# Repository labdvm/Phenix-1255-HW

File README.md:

<p align="center">
  <picture>
    <source media="(prefers-color-scheme: dark)" srcset="documentation/images/phenix-1255_logo_white.png">
    
  </picture>
</p>

<p align="center">
  <b>"Pi-less" SX1255 RF shield for the NXP FRDM-MCXN947</b><br>
  KiCad hardware design · separate RX/TX paths · 38.4 MHz TCXO · HS USB or Ethernet via the FRDM board
</p>

<p align="center">

</p>

<p align="center">
  <a href="#overview">Overview</a> ·
  <a href="#board-variants">Board variants</a> ·
  <a href="#features">Features</a> ·
  <a href="#preview">Preview</a> ·
  <a href="#documentation">Documentation</a> ·
  <a href="#repository-contents">Repository contents</a> ·
  <a href="#getting-started">Getting started</a> ·
  <a href="#license">License</a>
</p>

## Overview

Phenix-1255 is a shield board that pairs the popular **Semtech SX1255** RF transceiver with the
**NXP FRDM-MCXN947** development board — no Raspberry Pi required. The MCX N947 handles the
I/Q sample stream and talks to the host PC over **High-Speed USB** or **Ethernet**.

The project idea comes from **[DM5LF](https://github.com/w4tchd0g)**, who also writes the software. The hardware was designed by **[Z32IT](https://github.com/labdvm)**.

| | |
|---|---|
| 🧠 **Controller** | NXP FRDM-MCXN947 (plugs directly onto the shield headers) |
| 📡 **RF transceiver** | Semtech SX1255 (I/Q, 400–510 MHz) |
| ⏱️ **Reference clock** | 38.4 MHz TCXO, 0.5–1 ppm |
| 🔌 **Host link** | High-Speed USB 2.0 or Ethernet of the FRDM-MCXN947 |
| ⚡ **Power** | 5 V from the FRDM-MCXN947 (USB-C); PoE operation possible with a 48 V → 5 V USB-C PoE splitter |
| 📐 **PCB** | 118 × 55 mm, 2 layers, 1.2 mm thickness |

## Board variants

The repository contains two variants of revision V2. Both share the same board outline, headers,
power supply, user interface and RX path.

| Variant | Folder | Difference |
|---|---|---|
| **V2** | [`FRDM-SX1255/`](FRDM-SX1255) | SX1255 TX output → low-pass filter → U.FL |
| **V2 Plus** | [`FRDM-SX1255+/`](FRDM-SX1255+) | Additional **TX driver amplifier** (Qorvo TQP3M9036, U2) between the SX1255 and the low-pass filter, with a resistive π-attenuator (R10–R12) at its input. The amplifier runs from 5 V and is switched together with the PA via `~PA_EN`. |

## Features

- **Separate RX and TX paths** with U.FL connectors (*TX* JJ1, *RX* JJ2)
  - RX: SAW band-pass filter (Tai-Saw TA0655A, 430 MHz centre frequency, 2 MHz bandwidth) → LC matching → `RFI`
  - TX: `RFO_P` → low-pass filter (Mini-Circuits LFCN-490+) → U.FL; V2 Plus adds the TQP3M9036 driver amplifier
- **Switchable PA supply** – P-MOSFET (DMP1045U) controlled by `~PA_EN`
- **Power supply** – resettable 500 mA fuse, TVS diode array (SP0502BAHT), ferrite bead and 3.3 V LDO (MCP1703)
- **User interface**
  - Three push buttons: *Left*, *OK*, *Right*
  - Socket for an I²C OLED display
  - Status LEDs: *PWR*, *Good*, *Info*, *Err*

## Preview

### V2

| Top | Bottom |
|:---:|:---:|
|  |  |

### V2 Plus

| Top | Bottom |
|:---:|:---:|
|  |  |

The images are rendered from the `.kicad_pcb` files with the KiCad 3D renderer and show the fully
assembled board with a 0.96″ OLED module plugged into its socket (J7), including the parts that are
marked *do not populate* in the layout (FRDM headers, OLED socket and, on V2 Plus, the SAW filter).
After changing the layout, run [`./scripts/render.sh`](scripts/render.sh) to update the images.

### 3D models

Every part on the board has a 3D model, so the board can be checked mechanically (e.g. for an
enclosure) and exported as STEP from KiCad. Most models come from the KiCad standard library
(`${KICAD10_3DMODEL_DIR}`); parts without a matching library model use these substitutes:

| Part | Footprint | 3D model | Source |
|---|---|---|---|
| FRDM headers J1, J2, J3, J4, J9, J12 | Samtec SSQ (FRDM template) | `PinHeader_2xNN_P2.54mm_Vertical` | KiCad library, mounted below the board |
| U.FL connectors JJ1 *TX* / JJ2 *RX* | `U.FL_Molex_MCRF_73412-0110_Vertical` | `U.FL_Hirose_U.FL-R-SMT-1_Vertical`, rotated 90° | KiCad library (no model for the Molex footprint) |
| Push buttons SW1–SW3 | `PTS647SK38SMTR2LFS` | `SW_SPST_PTS647Sx70` (stand-in for the E-Switch TL3305 in the BOM) | KiCad library |
| SAW filter X1 (TA0655A) | `Filter_SAW-6_3.8x3.8mm` | [`3dmodels/TA0655A.stp`](FRDM-SX1255/3dmodels/TA0655A.stp) | Project file |
| TX amplifier U2 (V2 Plus) | `SON50P200X200X95-9N` | `VDFN-8-1EP_2x2mm_P0.5mm_EP0.9x1.7mm` | KiCad library |
| OLED display (plugged into J7) | `PinSocket_1x04_P2.54mm_Vertical` | [`3dmodels/OLED_0.96in_128x64_I2C.stp`](FRDM-SX1255/3dmodels/OLED_0.96in_128x64_I2C.stp) – 0.96″ 128×64 SSD1306 I²C module, as a second model on the socket | Project file |

Mounting holes need no model.

The shield is designed for the NXP FRDM-MCXN947 development board, see the
[NXP FRDM-MCXN947 product page](https://www.nxp.com/design/design-center/development-boards-and-designs/FRDM-MCXN947)
for photos, documentation and the board pinout.

## Documentation

| Document | Content |
|---|---|
| [Hardware](documentation/hardware.md) | Block overview, header pin assignment, PA supply, power supply, V2 Plus amplifier, changes in the current layout |
| [Manufacturing and assembly](documentation/manufacturing.md) | PCB specification, production files, assembly notes, first power-up |

## Host PC requirements

| Component | Minimum |
|---|---|
| Interface | USB 2.0 (High-Speed) or Ethernet |
| CPU | Intel or AMD, 4 cores |
| RAM | 4 GB DDR3 |
| Storage | SSD |
| OS | Xubuntu x64 |

## Repository contents

Each board variant is a self-contained KiCad project in its own folder:

```
Phenix-1255-HW/
├── FRDM-SX1255/                      # V2
│   ├── FRDM-SX1255-V2.kicad_pro      # KiCad project – open this one
│   ├── FRDM-SX1255-V2.kicad_sch      # schematic
│   ├── FRDM-SX1255-V2.kicad_pcb      # PCB layout
│   ├── FRDM-SX1255-V2.pdf            # schematic as PDF
│   ├── FRDM-SX1255-V2.png / _b.png   # 2D board views (KiCad export)
│   ├── 3dmodels/                     # project-specific 3D models
│   └── Gerber and BOM/               # manufacturing data
│       ├── …_gerber.zip              # Gerber and drill files for PCB fabrication
│       ├── …_bom.csv                 # bill of materials (incl. DigiKey part numbers)
│       ├── …_positions.csv           # pick-and-place positions for assembly
│       └── …_netlist.ipc             # IPC-D-356 netlist for electrical testing
├── FRDM-SX1255+/                     # V2 Plus – same structure, files named "FRDM-SX1255+ V2.*"
├── documentation/                    # hardware and manufacturing documentation, images
└── scripts/render.sh                 # renders the PCB images (needs kicad-cli)
```

| Quick links | V2 | V2 Plus |
|---|---|---|
| Schematic (PDF) | [`FRDM-SX1255-V2.pdf`](FRDM-SX1255/FRDM-SX1255-V2.pdf) | [`FRDM-SX1255+ V2.pdf`](FRDM-SX1255+/FRDM-SX1255+%20V2.pdf) |
| Gerber | [`…_gerber.zip`](FRDM-SX1255/Gerber%20and%20BOM/FRDM-SX1255-V2.kicad_pcb_gerber.zip) | [`…_gerber.zip`](FRDM-SX1255+/Gerber%20and%20BOM/FRDM-SX1255+%20V2.kicad_pcb_gerber.zip) |
| BOM | [`…_bom.csv`](FRDM-SX1255/Gerber%20and%20BOM/FRDM-SX1255-V2.kicad_pcb_bom.csv) | [`…_bom.csv`](FRDM-SX1255+/Gerber%20and%20BOM/FRDM-SX1255+%20V2.kicad_pcb_bom.csv) |
| Positions | [`…_positions.csv`](FRDM-SX1255/Gerber%20and%20BOM/FRDM-SX1255-V2.kicad_pcb_positions.csv) | [`…_positions.csv`](FRDM-SX1255+/Gerber%20and%20BOM/FRDM-SX1255+%20V2.kicad_pcb_positions.csv) |

## Getting started

1. **Choose a variant** – V2, or V2 Plus if you want the additional TX driver amplifier.
2. **Order the PCB** – upload the Gerber ZIP to a PCB manufacturer of your choice
   (2 layers, **1.2 mm** board thickness). For assembly, provide the BOM and position files as well.
   Details: [Manufacturing and assembly](documentation/manufacturing.md).
3. **Assemble** the shield and plug it onto the FRDM-MCXN947.
4. **Connect antennas / RF cabling** to the U.FL connectors *TX* (JJ1) and *RX* (JJ2).
5. **Install the software** from [phenix-1255-sw](https://github.com/w4tchd0g/phenix-1255-sw).

## Related projects

- 💻 **Software:** [w4tchd0g/phenix-1255-sw](https://github.com/w4tchd0g/phenix-1255-sw)

## Credits

- **Idea & software:** DM5LF – [@w4tchd0g](https://github.com/w4tchd0g)
- **Hardware design:** Z32IT – [@labdvm](https://github.com/labdvm)

## License

Copyright © Z32IT 2026.

This source describes Open Hardware and is licensed under the **CERN-OHL-P v2**.

You may redistribute and modify this source and make products using it under the terms of the
[CERN-OHL-P v2](https://ohwr.org/cern_ohl_p_v2.txt). This source is distributed **WITHOUT ANY EXPRESS
OR IMPLIED WARRANTY, INCLUDING OF MERCHANTABILITY, SATISFACTORY QUALITY AND FITNESS FOR A PARTICULAR
PURPOSE**. Please see the CERN-OHL-P v2 for applicable conditions.

Source location: <https://github.com/labdvm/Phenix-1255-HW>

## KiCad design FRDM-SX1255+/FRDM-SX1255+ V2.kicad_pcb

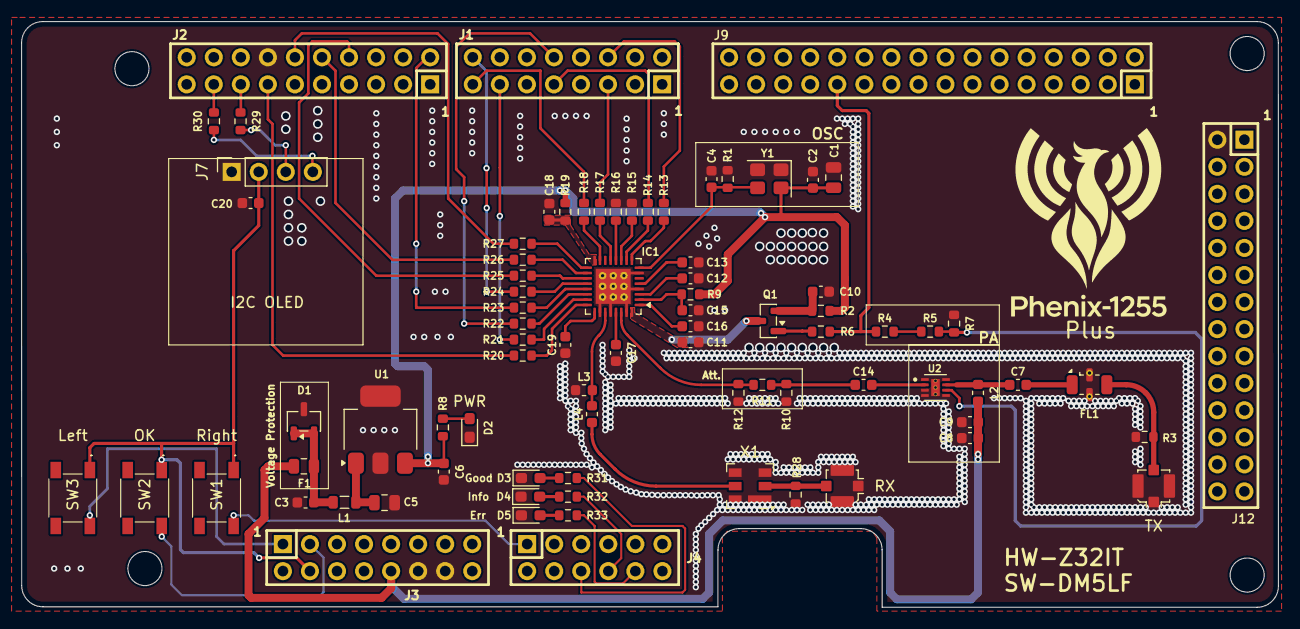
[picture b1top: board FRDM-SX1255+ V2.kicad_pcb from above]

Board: 2 copper layers, 118.0 x 55.0 mm, 86 parts (0 on the bottom side), 66 nets.

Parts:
C1, C5: 22u; C_0805_2012Metric
C2, C11, C12, C13, C19, C20: 100n; C_0603_1608Metric
C3, C6, C8, C10, C15, C18: 1u; C_0603_1608Metric
C4: 10p; C_0603_1608Metric
C7, C9, C14, C17: 100p; C_0603_1608Metric
C16: 10n; C_0603_1608Metric
D1: SP0502BAHT; SOT-23-3
D2: PWR; LED_0603_1608Metric_Pad1.05x0.95mm_HandSolder
D3: Good; LED_0603_1608Metric_Pad1.05x0.95mm_HandSolder
D4: Info; LED_0603_1608Metric_Pad1.05x0.95mm_HandSolder
D5: Err; LED_0603_1608Metric_Pad1.05x0.95mm_HandSolder
F1: 500mA; Fuse_0805_2012Metric
FL1: LFCN-490; Filter_Mini-Circuits_FV1206
H1, H2, H3, H4: Mechanical_MountingHole; MOUNTINGHOLE_3.2MM_M3
IC1: SX1255; QFN-32-1EP_5x5mm_P0.5mm_EP3.3x3.3mm_ThermalVias
J1, J3: SSQ-108-03-T-D
J2: SSQ-110-03-T-D
J4: SSQ-106-03-T-D
J7: I2C OLED; PinSocket_1x04_P2.54mm_Vertical
J9: SSQ-116-03-T-D
J12: SSQ-114-03-T-D
JJ1: TX; U.FL_Molex_MCRF_73412-0110_Vertical
JJ2: RX; U.FL_Molex_MCRF_73412-0110_Vertical
L1: 600 ohm/100MHz; L_0805_2012Metric
L2: 68nH; L_0603_1608Metric
L3: 82n; L_0603_1608Metric
L4: 39n; L_0603_1608Metric
Q1: DMP1045U; SOT-23
R1, R7: 10K; R_0603_1608Metric
R2, R4, R9, R19: 1R; R_0603_1608Metric
R3, R28: 1M; R_0603_1608Metric
R5: 33K; R_0603_1608Metric
R6, R15, R16, R17, R24, R25, R27: 330R; R_0603_1608Metric
R8: 3K3; R_0603_1608Metric
R10, R12: 150R; R_0603_1608Metric
R11: 36R; R_0603_1608Metric
R13, R14, R18, R20, R21, R22, R23, R26, R29, R30: 33R; R_0603_1608Metric
R31, R32, R33: 1K5; R_0603_1608Metric
SW1: Right; PTS647SK38SMTR2LFS
SW2: OK; PTS647SK38SMTR2LFS
SW3: Left; PTS647SK38SMTR2LFS
U1: MCP1703Ax-330xxDB; SOT-223-3_TabPin2
U2: TQP3M9036; SON50P200X200X95-9N
X1: TA0655A; Filter_SAW-6_3.8x3.8mm
Y1: 38.4MHz; Crystal_SMD_3225-4Pin_3.2x2.5mm

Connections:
+3V3: C1.2, C2.1, C6.1, R2.2, R8.2, R9.2, R19.1, U1.3 (VO), Y1.4 (VDD)
+5V0: C8.2, C9.1, F1.1, J3.10, L2.1
/+3.3V: C20.2, J3.4, J7.2, SW1.1, SW2.1, SW3.1
/BTN_LEFT: J3.1, SW3.2
/BTN_OK: J3.3, SW2.2
/BTN_RIGHT: J4.1, SW1.2
/CK_OUT: J1.9, R14.1
/DIO0: J2.2, R23.1
/DIO1: J1.10, R22.1
/DIO2: J1.13, R21.1
/DIO3: J2.13, R20.1
/I_IN: J1.5, R17.1
/I_OUT: J1.15, R18.1
/MISO: J2.10, R26.1
/MOSI: J2.8, R25.1
/NSS: J1.16, R24.1
/RF-out: C7.1, L2.2, U2.7
/RST: J1.6, R13.1
/SCK: J2.12, R27.1
/SCL_oled: J2.15, R29.2
/SDA_oled: J2.17, R30.2
/SX_CK_IN: IC1.11 (CK_IN), R15.2
/SX_CK_OUT: IC1.10 (CK_OUT), R14.2
/SX_DIO0: IC1.21 (DIO0), R23.2
/SX_DIO1: IC1.22 (DIO1), R22.2
/SX_DIO2: IC1.23 (DIO2), R21.2
/SX_DIO3: IC1.24 (DIO3), R20.2
/SX_I_IN: IC1.13 (I_IN), R17.2
/SX_I_OUT: IC1.15 (I_OUT), R18.2
/SX_MISO: IC1.18 (MISO), R26.2
/SX_MOSI: IC1.19 (MOSI), R25.2
/SX_NSS: IC1.20 (NSS), R24.2
/SX_Q_IN: IC1.12 (Q_IN), R16.2
/SX_RESET: IC1.9 (RESET), R13.2
/SX_RFI: IC1.27 (RFI), L3.2, L4.2
/SX_RFO_N: C17.2, IC1.29 (RFO_N)
/SX_RFO_P: IC1.30 (RFO_P), R11.1, R12.1
/SX_SCK: IC1.17 (SCK), R27.2
/SX_VBAT2: C18.1, IC1.16 (VBAT2), R19.2
/SX_VBAT3: C11.1, IC1.32 (VBAT3), Q1.3 (D)
/SX_VBATI: C15.1, IC1.2 (VBATI), R9.1
/SX_VR_ANA2: C19.2, IC1.25 (VR_ANA2)
/SX_VR_ANAI: C12.2, IC1.3 (VR_ANAI)
/SX_VR_DIG: C13.2, IC1.5 (VR_DIG)
/SX_VR_PA: C16.2, IC1.1 (VR_PA)
/TCXO: C4.1, IC1.8 (XTB), R1.1, Y1.3 (OUT)
/~PA_EN: J9.23 (Pin_23_23), R4.2, R6.1
GND: C1.1, C2.2, C3.2, C4.2, C5.2, C6.2, C8.1, C9.2, C10.2, C11.2, C12.1, C13.1, C15.2, C16.1, C17.1, C18.2, C19.1, C20.1, D1.3 (A), D2.1 (K), D3.1 (K), D4.1 (K), D5.1 (K), FL1.2 (GND), FL1.4 (GND), IC1.4 (GND_1), IC1.7 (GND_2), IC1.26 (GND_3), IC1.28 (GND_4), IC1.31 (GND_5), IC1.33 (GND_6), J2.14, J3.12, J3.14, J7.1, J12.2, JJ1.2 (Ext), JJ2.2 (Ext), L3.1, R1.2, R3.1, R7.1, R10.2, R12.2, R15.1, R16.1, R28.1, U1.2 (GND), U2.1, U2.3, U2.4, U2.5, U2.8, U2.9, U2.V1, U2.V2, U2.V3, X1.1 (GND), X1.3 (GND), X1.4 (GND), X1.6 (GND), Y1.1 (Tri-State), Y1.2 (GND)
unnamed: C3.1, D1.1 (K), D1.2 (K), F1.2, L1.1
unnamed: C14.1, R10.1, R11.2
unnamed: C14.2, U2.2
unnamed: D2.2 (A), R8.1
unnamed: D3.2 (A), R31.2
unnamed: D4.2 (A), R32.2
unnamed: D5.2 (A), R33.2
unnamed: C7.2, FL1.1 (IN)
unnamed: FL1.3 (OUT), JJ1.1 (In), R3.2
unnamed: J7.3, R29.1
unnamed: J7.4, R30.1
unnamed: JJ2.1 (In), R28.2, X1.2 (IN)
unnamed: Q1.1 (G), R6.2
unnamed: C10.1, Q1.2 (S), R2.1
unnamed: R4.1, R5.2
unnamed: R5.1, R7.2, U2.6
unnamed: C5.1, L1.2, U1.1 (VI)
unnamed: L4.1, X1.5 (OUT)

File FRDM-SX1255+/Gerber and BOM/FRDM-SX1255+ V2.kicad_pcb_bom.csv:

Designator,Quantity,Value,Footprint,Package,MPN,DNP,Mount_Type,KiLib_Generator,Manufacturer,Manufacturer Product Number,Description,DigiKey Part Number,Sim.Pin,TCXO-Footprints
"C1, C5",2,22u,C_0805_2012Metric,,1276-6526-1-ND,,smt,SMD_2terminal_chip_molded,Samsung Electro-Mechanics,CL21A226KOQNNNE,,,,
"C10, C15, C18, C3, C6, C8",6,1u,C_0603_1608Metric,,311-3484-1-ND,,smt,SMD_2terminal_chip_molded,YAGEO,CC0603JRX7R6BB105,,,,
"C11, C12, C13, C19, C2, C20",6,100n,C_0603_1608Metric,,720-1688-1-ND,,smt,SMD_2terminal_chip_molded,Vishay Vitramon,VJ0603Y104JXQPW1BC,,,,
"C14, C17, C7, C9",4,100p,C_0603_1608Metric,,399-15348-1-ND,,smt,SMD_2terminal_chip_molded,KEMET,C0603C101J8GACTU,,,,
C16,1,10n,C_0603_1608Metric,,399-C0603C103K8RACTUCT-ND,,smt,SMD_2terminal_chip_molded,KEMET,C0603C103K8RACTU,,,,
C4,1,10p,C_0603_1608Metric,,399-14932-1-ND,,smt,SMD_2terminal_chip_molded,KEMET,C0603C100J8GACTU,,,,
D1,1,SP0502BAHT,SOT-23-3,,,,smt,package/gullwing,Littelfuse Inc.,SP0502BAHTG,"TVS Diode Array, 5.5V Standoff, 2 Channels, SOT-23 package",F2714CT-ND,,
D2,1,PWR,LED_0603_1608Metric_Pad1.05x0.95mm_HandSolder,,160-LTST-T180UWETCT-ND,,smt,SMD_2terminal_chip_molded,Lite-On Inc.,LTST-T180UWET,"Light emitting diode, small symbol",,1=K 2=A,
D3,1,Good,LED_0603_1608Metric_Pad1.05x0.95mm_HandSolder,,754-APT1608SGD3CT-ND,,smt,SMD_2terminal_chip_molded,Kingbright,APT1608SGD3,"Light emitting diode, small symbol",,1=K 2=A,
D4,1,Info,LED_0603_1608Metric_Pad1.05x0.95mm_HandSolder,,160-1437-1-ND,,smt,SMD_2terminal_chip_molded,Lite-On Inc.,LTST-C190KSKT,"Light emitting diode, small symbol",,1=K 2=A,
D5,1,Err,LED_0603_1608Metric_Pad1.05x0.95mm_HandSolder,,160-1479-1-ND,,smt,SMD_2terminal_chip_molded,Lite-On Inc.,LTST-S270KRKT,"Light emitting diode, small symbol",,1=K 2=A,
F1,1,500mA,Fuse_0805_2012Metric,,,,smt,SMD_2terminal_chip_molded,Littelfuse Inc.,0805L050WR,"Resettable fuse, polymeric positive temperature coefficient, small symbol",F2772CT-ND,,
FL1,1,LFCN-490,Filter_Mini-Circuits_FV1206,,3157-LFCN-490+CT-ND,,smt,,Mini-Circuits,LFCN-490+,,,,
"H1, H2, H3, H4",4,Mechanical_MountingHole,MOUNTINGHOLE_3.2MM_M3,,,,tht,,,,,,,
IC1,1,SX1255,QFN-32-1EP_5x5mm_P0.5mm_EP3.3x3.3mm_ThermalVias,,SX1255IWLTRTCT-ND,,smt,package/no_lead,Semtech Corporation,SX1255IWLTRT,,,,
J9,1,~,SSQ-116-03-T-D,,,,tht,,,,"Generic connector, double row, 02x16, odd/even pin numbering scheme (row 1 odd numbers, row 2 even numbers), script generated (kicad-library-utils/schlib/autogen/connector/)",,,
JJ1,1,TX,U.FL_Molex_MCRF_73412-0110_Vertical,,343-CONMHF1-SMD-G-TCT-ND,,smt,,TE Connectivity Linx,CONMHF1-SMD-G-T,,,,
JJ2,1,RX,U.FL_Molex_MCRF_73412-0110_Vertical,,343-CONMHF1-SMD-G-TCT-ND,,smt,,TE Connectivity Linx,CONMHF1-SMD-G-T,,,,
L1,1,600 ohm/100MHz,L_0805_2012Metric,,490-1046-1-ND,,smt,SMD_2terminal_chip_molded,Murata Electronics,BLM21BD601SN1D,FERRITE BEAD 600 OHM 0805 1LN,,,
L2,1,68nH,L_0603_1608Metric,,490-1178-1-ND,,smt,SMD_2terminal_chip_molded,Murata Electronics,LQW18AN68NJ00D,,,,
L3,1,82n,L_0603_1608Metric,,490-LQW18AS82NG00DCT-ND,,smt,SMD_2terminal_chip_molded,Murata Electronics,LQW18AS82NG00D,,,,
L4,1,39n,L_0603_1608Metric,,490-LQW18AS39NG00DCT-ND,,smt,SMD_2terminal_chip_molded,Murata Electronics,LQW18AS39NG00D,,,,
Q1,1,DMP1045U,SOT-23,,BSS84-TPMSCT-ND,,smt,package/gullwing,Diodes Incorporated,DMP1045UQ-7,P-Channel 12 V 2.6A (Ta) 530mW,31-DMP1045UQ-7CT-ND,,
"R1, R7",2,10K,R_0603_1608Metric,,541-10.0KHCT-ND,,smt,SMD_2terminal_chip_molded,Vishay Dale,CRCW060310K0FKEA,,,,
"R10, R12",2,150R,R_0603_1608Metric,,YAG1533CT-ND,,smt,SMD_2terminal_chip_molded,YAGEO,RT0603BRD07150RL,,,,
R11,1,36R,R_0603_1608Metric,,13-RT0603BRC0736RLCT-ND,,smt,SMD_2terminal_chip_molded,YAGEO,RT0603BRC0736RL,,,,
"R13, R14, R18, R20, R21, R22, R23, R26, R29, R30",10,33R,R_0603_1608Metric,,541-33.0HCT-ND,,smt,SMD_2terminal_chip_molded,Vishay Dale,CRCW060333R0FKEA,,,,
"R15, R16, R17, R24, R25, R27, R6",7,330R,R_0603_1608Metric,,541-330HCT-ND,,smt,SMD_2terminal_chip_molded,Vishay Dale,CRCW0603330RFKEA,,,,
"R19, R2, R9",3,1R,R_0603_1608Metric,,P17371CT-ND,,smt,SMD_2terminal_chip_molded,Panasonic Industry,ERJ-3BQF1R0V,,,,
"R28, R3",2,1M,R_0603_1608Metric,,541-1.00MHCT-ND,,smt,SMD_2terminal_chip_molded,Vishay Dale,CRCW06031M00FKEA,,,,
"R31, R32, R33",3,1K5,R_0603_1608Metric,,541-1.5KGCT-ND,,smt,SMD_2terminal_chip_molded,Vishay Dale,CRCW06031K50JNEA,,,,
R4,1,1R,R_0603_1608Metric,,541-1.00HHCT-ND,,smt,SMD_2terminal_chip_molded,Vishay Dale,CRCW06031R00FKEA,,,,
R5,1,33K,R_0603_1608Metric,,541-33.0KHCT-ND,,smt,SMD_2terminal_chip_molded,Vishay Dale,CRCW060333K0FKEA,,,,
R8,1,3K3,R_0603_1608Metric,,541-3.30KHCT-ND,,smt,SMD_2terminal_chip_molded,Vishay Dale,CRCW06033K30FKEA,,,,
SW1,1,Right,PTS647SK38SMTR2LFS,,,,smt,,E-Switch,TL3305CF260QG,"Push button switch, generic, two pins",EG5355CT-ND,,
SW2,1,OK,PTS647SK38SMTR2LFS,,,,smt,,E-Switch,TL3305CF260QG,"Push button switch, generic, two pins",EG5355CT-ND,,
SW3,1,Left,PTS647SK38SMTR2LFS,,,,smt,,E-Switch,TL3305CF260QG,"Push button switch, generic, two pins",EG5355CT-ND,,
U1,1,MCP1703Ax-330xxDB,SOT-223-3_TabPin2,,MCP1703T-3302E/DBCT-ND,,smt,,Microchip Technology,MCP1703T-3302E/DB,,,,
U2,1,TQP3M9036,SON50P200X200X95-9N,,2312-TQP3M9036CT-ND,,smt,,Qorvo,TQP3M9036,,,,
Y1,1,38.4MHz,Crystal_SMD_3225-4Pin_3.2x2.5mm,,114-TG2520SMN38.4000M-MCGNNM3CT-ND,,smt,crystal_resonator_oscillator,EPSON ,TG2520SMN 38.4000M-MCGNNM3,Clipped SW/0.5~1ppm,,,3225 or 2510

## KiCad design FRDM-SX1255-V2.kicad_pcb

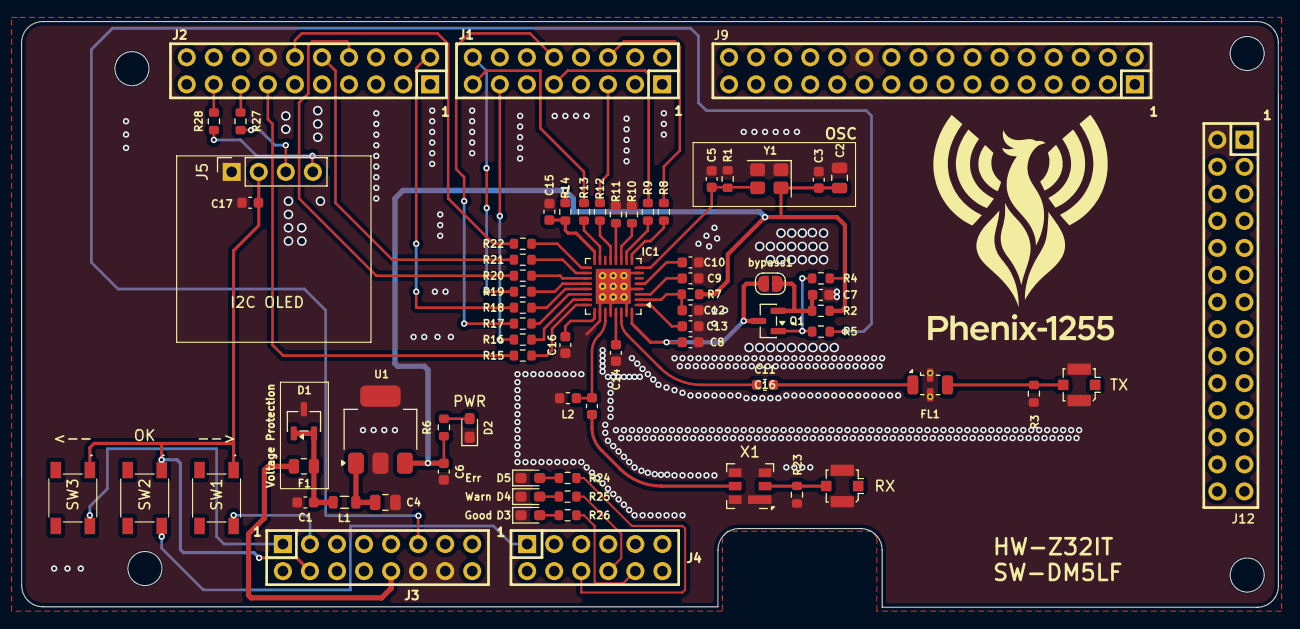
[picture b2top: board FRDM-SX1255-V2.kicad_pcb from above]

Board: 2 copper layers, 118.0 x 55.0 mm, 77 parts (0 on the bottom side), 61 nets.

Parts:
C1, C6, C7, C12, C15: 1u; C_0603_1608Metric
C2, C4: 22u; C_0805_2012Metric
C3, C8, C9, C10, C16, C17: 100n; C_0603_1608Metric
C5: 10p; C_0603_1608Metric
C11, C14: 100p; C_0603_1608Metric
C13: 10n; C_0603_1608Metric
D1: SP0502BAHT; SOT-23-3
D2: PWR; LED_0603_1608Metric_Pad1.05x0.95mm_HandSolder
D3: Good; LED_0603_1608Metric_Pad1.05x0.95mm_HandSolder
D4: Warn; LED_0603_1608Metric_Pad1.05x0.95mm_HandSolder
D5: Err; LED_0603_1608Metric_Pad1.05x0.95mm_HandSolder
F1: 500mA; Fuse_0805_2012Metric
FL1: LFCN-490; Filter_Mini-Circuits_FV1206
H1, H2, H3, H4: Mechanical_MountingHole; MOUNTINGHOLE_3.2MM_M3
IC1: SX1255; QFN-32-1EP_5x5mm_P0.5mm_EP3.3x3.3mm_ThermalVias
J1, J3: SSQ-108-03-T-D
J1#2: TX; U.FL_Molex_MCRF_73412-0110_Vertical
J2: RX; U.FL_Molex_MCRF_73412-0110_Vertical
J2#2: SSQ-110-03-T-D
J4: SSQ-106-03-T-D
J5: I2C OLED; PinSocket_1x04_P2.54mm_Vertical
J9: SSQ-116-03-T-D
J12: SSQ-114-03-T-D
L1: 600 ohm/100MHz; L_0805_2012Metric
L2: 82n; L_0603_1608Metric
L3: 39n; L_0603_1608Metric
Q1: BSS84; SOT-23
R1, R4: 10K; R_0603_1608Metric
R2, R7, R14: 1R; R_0603_1608Metric
R3, R23: 1M; R_0603_1608Metric
R5, R10, R11, R12, R19, R20, R22: 330R; R_0603_1608Metric
R6: 3K3; R_0603_1608Metric
R8, R9, R13, R15, R16, R17, R18, R21, R27, R28: 33R; R_0603_1608Metric
R24, R25, R26: 1K5; R_0603_1608Metric
SW1: -->; PTS647SK38SMTR2LFS
SW2: OK; PTS647SK38SMTR2LFS
SW3: <--; PTS647SK38SMTR2LFS
U1: MCP1703Ax-330xxDB; SOT-223-3_TabPin2
X1: TA0655A; Filter_SAW-6_3.8x3.8mm
Y1: 38.4MHz; Crystal_SMD_3225-4Pin_3.2x2.5mm
bypass1: Bypass; SolderJumper-2_P1.3mm_Open_RoundedPad1.0x1.5mm

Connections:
+3V3: C2.2, C3.1, C6.1, R2.2, R4.2, R6.2, R7.2, R14.1, U1.3 (VO), Y1.4 (VDD)
+5V0: F1.1, J3.10
/+3.3V: C17.2, J3.4, J5.2, SW1.1, SW2.1, SW3.1
/BTN_LEFT: J3.1, SW3.2
/BTN_OK: J4.1, SW2.2
/BTN_RIGHT: J3.3, SW1.2
/CK_OUT: J1.9, R9.1
/DIO0: J2#2.2, R18.1
/DIO1: J1.10, R17.1
/DIO2: J1.13, R16.1
/DIO3: J2#2.13, R15.1
/I_IN: J1.5, R12.1
/I_OUT: J1.15, R13.1
/MISO: J2#2.10, R21.1
/MOSI: J2#2.8, R20.1
/NSS: J1.16, R19.1
/RST: J1.6, R8.1
/SCK: J2#2.12, R22.1
/SCL_oled: J2#2.15, R27.2
/SDA_oled: J2#2.17, R28.2
/SX_CK_IN: IC1.11 (CK_IN), R10.2
/SX_CK_OUT: IC1.10 (CK_OUT), R9.2
/SX_DIO0: IC1.21 (DIO0), R18.2
/SX_DIO1: IC1.22 (DIO1), R17.2
/SX_DIO2: IC1.23 (DIO2), R16.2
/SX_DIO3: IC1.24 (DIO3), R15.2
/SX_I_IN: IC1.13 (I_IN), R12.2
/SX_I_OUT: IC1.15 (I_OUT), R13.2
/SX_MISO: IC1.18 (MISO), R21.2
/SX_MOSI: IC1.19 (MOSI), R20.2
/SX_NSS: IC1.20 (NSS), R19.2
/SX_Q_IN: IC1.12 (Q_IN), R11.2
/SX_RESET: IC1.9 (RESET), R8.2
/SX_RFI: IC1.27 (RFI), L2.2, L3.2
/SX_RFO_N: C14.2, IC1.29 (RFO_N)
/SX_RFO_P: C11.1, IC1.30 (RFO_P)
/SX_SCK: IC1.17 (SCK), R22.2
/SX_VBAT2: C15.1, IC1.16 (VBAT2), R14.2
/SX_VBAT3: C8.1, IC1.32 (VBAT3), Q1.3 (D), bypass1.2 (B)
/SX_VBATI: C12.1, IC1.2 (VBATI), R7.1
/SX_VR_ANA2: C16.2, IC1.25 (VR_ANA2)
/SX_VR_ANAI: C9.2, IC1.3 (VR_ANAI)
/SX_VR_DIG: C10.2, IC1.5 (VR_DIG)
/SX_VR_PA: C13.2, IC1.1 (VR_PA)
/TCXO: C5.1, IC1.8 (XTB), R1.1, Y1.3 (OUT)
/~PA_EN: J3.11, R5.1
GND: C1.2, C2.1, C3.2, C4.2, C5.2, C6.2, C7.2, C8.2, C9.1, C10.1, C12.2, C13.1, C14.1, C15.2, C16.1, C17.1, D1.3 (A), D2.1 (K), D3.1 (K), D4.1 (K), D5.1 (K), FL1.2 (GND), FL1.4 (GND), IC1.4 (GND_1), IC1.7 (GND_2), IC1.26 (GND_3), IC1.28 (GND_4), IC1.31 (GND_5), IC1.33 (GND_6), J1#2.2 (Ext), J2.2 (Ext), J2#2.14, J3.12, J3.14, J5.1, J9.22, J12.2, L2.1, R1.2, R3.1, R10.1, R11.1, R23.1, U1.2 (GND), X1.1 (GND), X1.3 (GND), X1.4 (GND), X1.6 (GND), Y1.1 (Tri-State), Y1.2 (GND)
unnamed: C1.1, D1.1 (K), D1.2 (K), F1.2, L1.1
unnamed: D2.2 (A), R6.1
unnamed: D3.2 (A), R26.2
unnamed: D4.2 (A), R25.2
unnamed: D5.2 (A), R24.2
unnamed: C11.2, FL1.1 (IN)
unnamed: FL1.3 (OUT), J1#2.1 (In), R3.2
unnamed: J2.1 (In), R23.2, X1.2 (IN)
unnamed: J5.3, R27.1
unnamed: J5.4, R28.1
unnamed: Q1.1 (G), R4.1, R5.2
unnamed: C7.1, Q1.2 (S), R2.1, bypass1.1 (A)
unnamed: C4.1, L1.2, U1.1 (VI)
unnamed: L3.1, X1.5 (OUT)

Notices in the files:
README.md:
License: CERN-OHL-P v2
